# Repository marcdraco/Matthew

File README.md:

# Matthew
High-performance headphone amplifier based on the NE5532DR

This is, I hope the last main revision for this project (third one is a charm) after I found I'd specificied the wrong value on the JLCPCB ordering page resulting in 100K resistors being replaced by 1 ohm ... and the Magic Smoke came without the genie... Oh well. This is why I ask everyone to wait until I've gotten final boards back and tested them before you spend your money on my mistakes. I wish I never made a mistake but you know, it's how we learn.

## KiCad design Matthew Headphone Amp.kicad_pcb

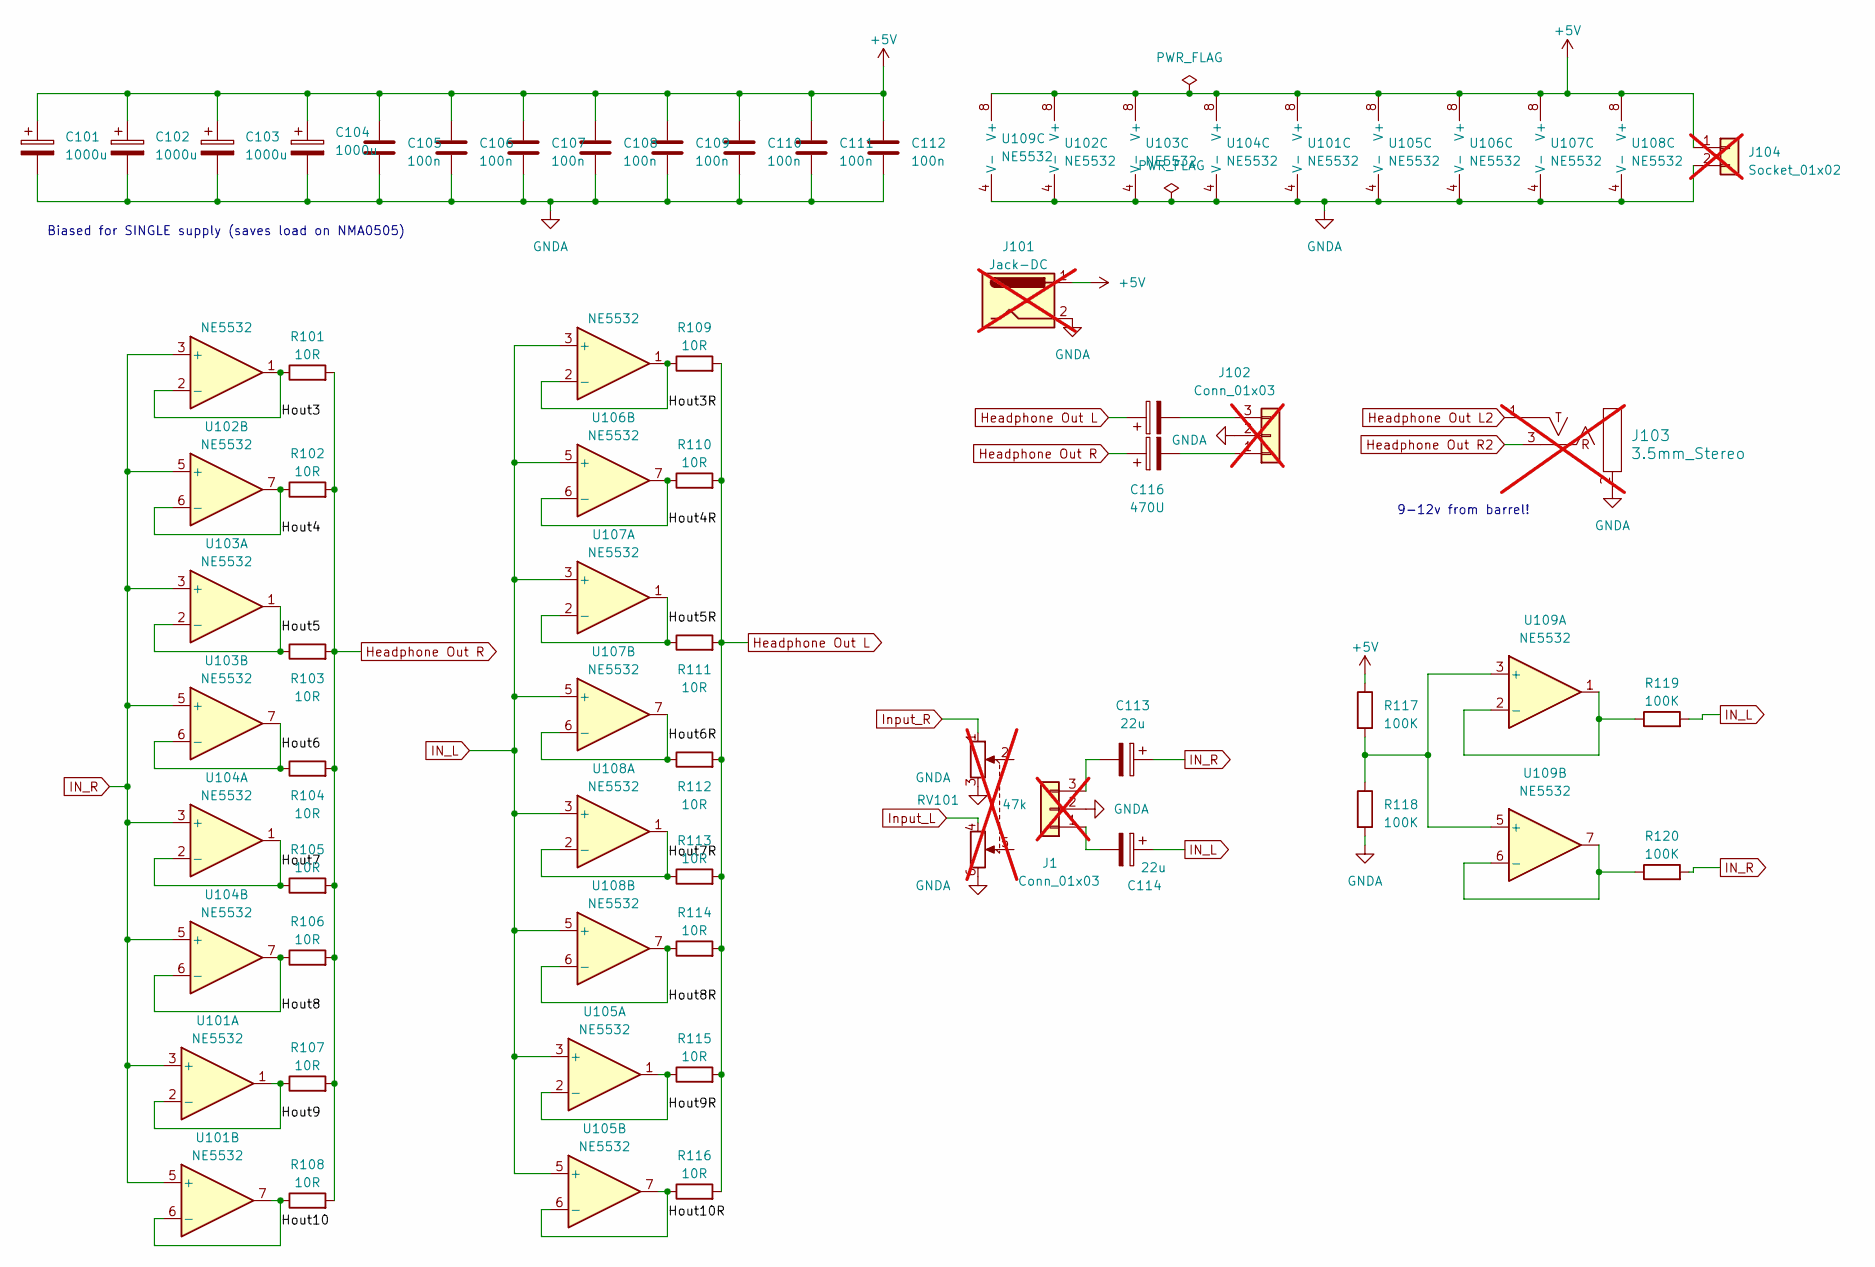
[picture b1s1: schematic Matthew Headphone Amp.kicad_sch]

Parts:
C101, C102, C103, C104: 1000u; C_Elec_10x10.2; MPN C3359
C105, C106, C107, C108, C109, C110, C111, C112: 100n; C_0603_1608Metric; MPN C14663
C113: 22u; C_1206_3216Metric; MPN C12891
C114: 22u; C_1206_3216Metric; MPN C12891; JLCPCBPart# C1289
C115, C116: 470U; C_Elec_8x10.2; MPN C2827943
J1, J102: Conn_01x03; PinHeader_1x03_P2.54mm_Vertical; Part Number 1-0301FBV0T; not fitted
J101: Jack-DC; PinHeader_1x02_P2.54mm_Vertical; not fitted
J103: 3.5mm_Stereo; EighthInch_Stereo_PJ366ST; Part Number WQP-WQP419GR; not fitted
J104: Socket_01x02; PinHeader_1x02_P2.54mm_Vertical; Part Number ?; not fitted
R101, R102, R103, R104, R105, R106, R107, R108, R109, R110, R111, R112, R113, R114, R115, R116: 10R; R_0805_2012Metric; MPN C17415
R117, R118, R119, R120: 100K; R_0603_1608Metric; MPN C25803
RV101: 47k; not fitted
U101, U102, U103, U104, U105, U106, U107, U108, U109: NE5532; SOIC-8_3.9x4.9mm_P1.27mm; MPN C7426

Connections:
+5V: C101.1, C102.1, C103.1, C104.1, C105.1, C106.1, C107.1, C108.1, C109.1, C110.1, C111.1, C112.1, J101.1, J104.1, R117.1, U101.8 (V+), U102.8 (V+), U103.8 (V+), U104.8 (V+), U105.8 (V+), U106.8 (V+), U107.8 (V+), U108.8 (V+), U109.8 (V+)
/Hout3: R101.1, U102.1, U102.2 (-)
/Hout3R: R109.1, U106.1, U106.2 (-)
/Hout4: R102.1, U102.6 (-), U102.7
/Hout4R: R110.1, U106.6 (-), U106.7
/Hout5: R103.1, U103.1, U103.2 (-)
/Hout5R: R111.1, U107.1, U107.2 (-)
/Hout6: R104.1, U103.6 (-), U103.7
/Hout6R: R112.1, U107.6 (-), U107.7
/Hout7: R105.1, U104.1, U104.2 (-)
/Hout7R: R113.1, U108.1, U108.2 (-)
/Hout8: R106.1, U104.6 (-), U104.7
/Hout8R: R114.1, U108.6 (-), U108.7
/Hout9: R107.1, U101.1, U101.2 (-)
/Hout9R: R115.1, U105.1, U105.2 (-)
/Hout10: R108.1, U101.6 (-), U101.7
/Hout10R: R116.1, U105.6 (-), U105.7
GNDA: C101.2, C102.2, C103.2, C104.2, C105.2, C106.2, C107.2, C108.2, C109.2, C110.2, C111.2, C112.2, J1.2, J101.2, J102.2, J103.2 (SHEILD), J104.2, R118.2, RV101.3, RV101.6, U101.4 (V-), U102.4 (V-), U103.4 (V-), U104.4 (V-), U105.4 (V-), U106.4 (V-), U107.4 (V-), U108.4 (V-), U109.4 (V-)
Headphone Out L: C115.1, R109.2, R110.2, R111.2, R112.2, R113.2, R114.2, R115.2, R116.2
Headphone Out R: C116.1, R101.2, R102.2, R103.2, R104.2, R105.2, R106.2, R107.2, R108.2
IN_L: C114.1, R119.2, U105.3 (+), U105.5 (+), U106.3 (+), U106.5 (+), U107.3 (+), U107.5 (+), U108.3 (+), U108.5 (+)
IN_R: C113.1, R120.2, U101.3 (+), U101.5 (+), U102.3 (+), U102.5 (+), U103.3 (+), U103.5 (+), U104.3 (+), U104.5 (+)
unnamed: C114.2, J1.1
unnamed: C113.2, J1.3
unnamed: C116.2, J102.1
unnamed: C115.2, J102.3
unnamed: R117.2, R118.1, U109.3 (+), U109.5 (+)
unnamed: R119.1, U109.1, U109.2 (-)
unnamed: R120.1, U109.6 (-), U109.7

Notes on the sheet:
Biased for SINGLE supply (saves load on NMA0505)
9-12v from barrel!

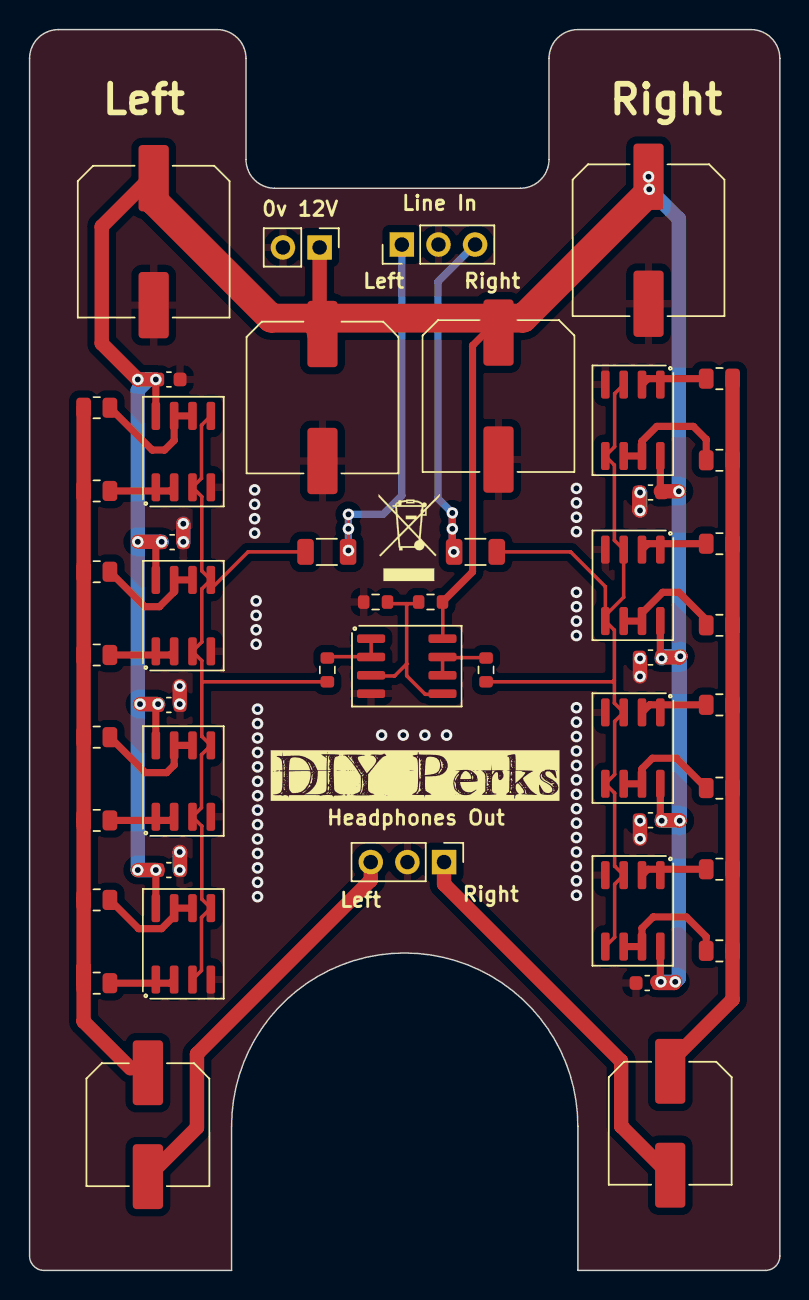
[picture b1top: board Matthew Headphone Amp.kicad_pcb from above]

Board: 2 copper layers, 52.0 x 86.0 mm, 48 parts (0 on the bottom side), 29 nets.

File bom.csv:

Designator,Footprint,Quantity,Value,LCSC Part #
"C101, C102, C103, C104",C_Elec_10x10.2,4,1000u,C3359
"C105, C106, C107, C108, C109, C110, C111, C112",0603,8,100n,C14663
"C113, C114",1206,2,22u,C12891
"C115, C116",C_Elec_8x10.2,2,470U,C2827943
"J1, J102",PinHeader_1x03_P2.54mm_Vertical,2,Conn_01x03,DNP
J104,PinHeader_1x02_P2.54mm_Vertical,1,Socket_01x02,DNP
"R101, R102, R103, R104, R105, R106, R107, R108, R109, R110, R111, R112, R113, R114, R115, R116",0805,16,10R,C17415
"R117, R118, R119, R120",0603,4,100K,C25803
"U101, U102, U103, U104, U105, U106, U107, U108, U109",SOIC-8_3.9x4.9mm_P1.27mm,9,NE5532,C7426
